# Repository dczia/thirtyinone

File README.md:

# thirtyinone
defcon 30 30-in-One badge

For those who don't like videos, here is a reasonable ordering of adding components:
* Pins (broken out all at once or a few at a time
* OLED Screen - top left, for pins
* Switches (next to battery, under keycaps hope)
* RGB LED - to the left of the other LEDS
* Speaker bottom right, on top of the spot of tape.  Polarity does not matter
* Battery case (big blank spot, bottom left)
* Key base (top right-should be obvious)
* Transformer (note THIS one is directional-the P side should line up with the P on the board)
* Potentiometer (next to the key base)
* Key Cap

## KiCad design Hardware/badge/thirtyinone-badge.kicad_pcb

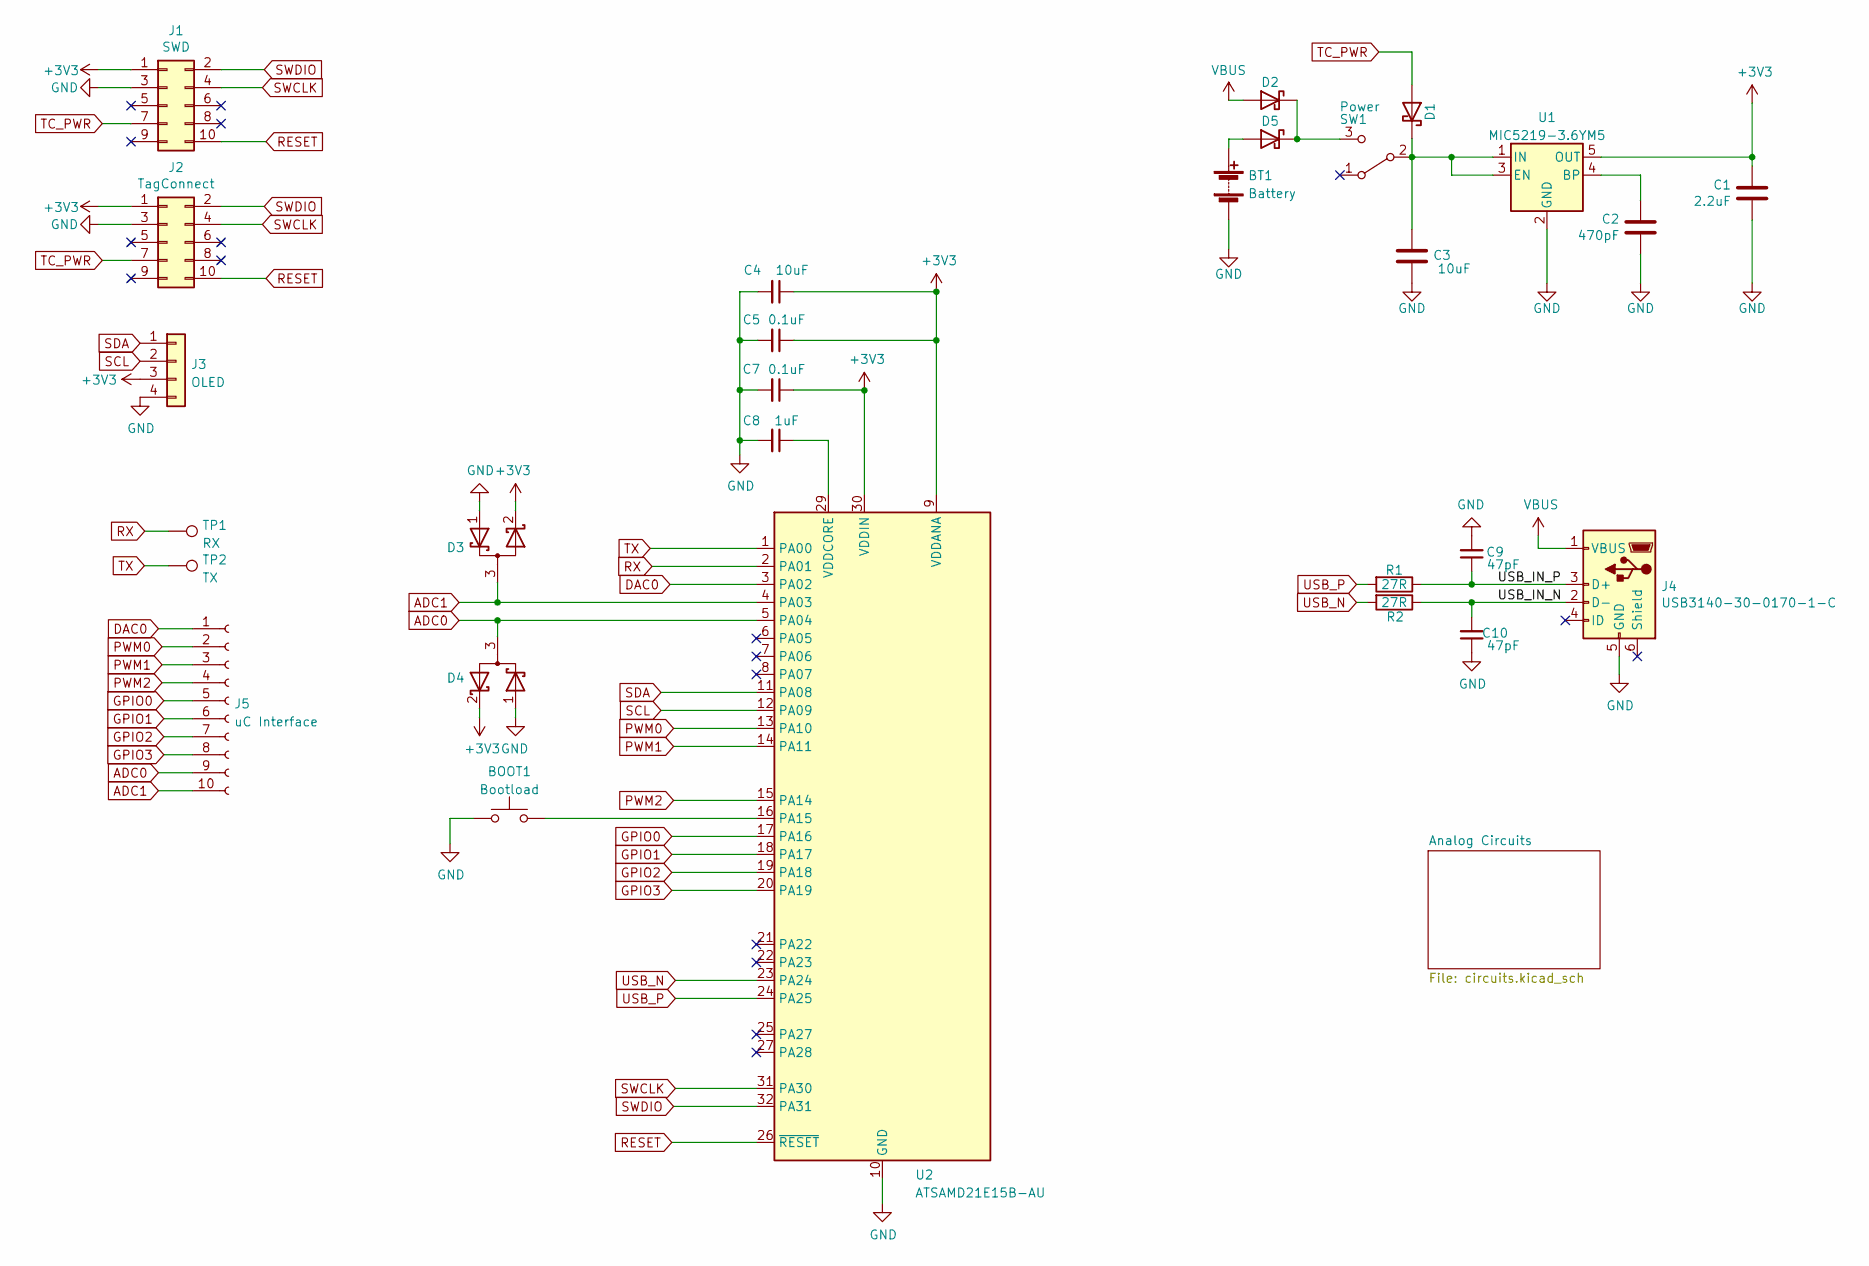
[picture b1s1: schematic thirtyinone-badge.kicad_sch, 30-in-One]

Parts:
BOOT1: Bootload; SW_Push_1P1T_NO_CK_PTS526
BT1: Battery; BatteryHolder_Keystone_2479_3xAAA
C1: 2.2uF; C_0805_2012Metric
C2: 470pF; C_0805_2012Metric
C3, C4: 10uF; C_0603_1608Metric
C5, C7: 0.1uF; C_0603_1608Metric
C8: 1uF; C_0603_1608Metric
C9, C10: 47pF; C_0603_1608Metric
D1, D2, D5: D_Schottky; D_SMA
D3, D4: D_Schottky_Dual_Series_ACK_Parallel; SOT-23
J1: SWD; PinHeader_2x05_P1.27mm_Vertical_Sneaky
J2: TagConnect; TC2050-NL_SMALL
J3: OLED; PinHeader_1x04_P2.54mm_Vertical
J4: USB3140-30-0170-1-C; USB31403001701C
J5: uC Interface; PinSocket_1x10_P2.54mm_Vertical
R1, R2: 27R; R_0603_1608Metric
SW1: Power; SW_E-Switch_EG1271_DPDT
TP1: RX; TestPoint_Pad_1.5x1.5mm
TP2: TX; TestPoint_Pad_1.5x1.5mm
U1: MIC5219-3.6YM5; SOT-23-5
U2: ATSAMD21E15B-AU; TQFP-32_7x7mm_P0.8mm

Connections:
+3V3: C1.1, C4.1, C5.1, C7.1, D3.2 (K), D4.2 (K), J1.1, J2.1, J3.3, U1.5 (OUT), U2.9 (VDDANA), U2.30 (VDDIN); also elsewhere on the board
/USB_IN_N: C10.2, J4.2 (D-), R2.1
/USB_IN_P: C9.1, J4.3 (D+), R1.1
ADC0: D4.3 (A), J5.9, U2.5 (PA04)
ADC1: D3.3 (A), J5.10, U2.4 (PA03)
DAC0: J5.1, U2.3 (PA02)
GND: BOOT1.1, BT1.2 (-), C1.2, C2.2, C3.2, C4.2, C5.2, C7.2, C8.2, C9.2, C10.1, D3.1 (K), D4.1 (K), J1.3, J2.3, J3.4, J4.5 (GND), U1.2 (GND), U2.10 (GND), U2.28 (GND); also elsewhere on the board
GPIO0: J5.5, U2.17 (PA16)
GPIO1: J5.6, U2.18 (PA17)
GPIO2: J5.7, U2.19 (PA18)
GPIO3: J5.8, U2.20 (PA19)
unnamed: BOOT1.2, U2.16 (PA15)
unnamed: BT1.1 (+), D5.2 (A)
unnamed: C2.1, U1.4 (BP)
unnamed: C3.1, D1.1 (K), SW1.2 (B), U1.1 (IN), U1.3 (EN)
unnamed: C8.1, U2.29 (VDDCORE)
unnamed: D2.1 (K), D5.1 (K), SW1.3 (C)
PWM0: J5.2, U2.13 (PA10)
PWM1: J5.3, U2.14 (PA11)
PWM2: J5.4, U2.15 (PA14)
RESET: J1.10, J2.10, U2.26 (~RESET)
RX: TP1.1, U2.2 (PA01)
SCL: J3.2, U2.12 (PA09)
SDA: J3.1, U2.11 (PA08)
SWCLK: J1.4, J2.4, U2.31 (PA30)
SWDIO: J1.2, J2.2, U2.32 (PA31)
TC_PWR: D1.2 (A), J1.7, J2.7
TX: TP2.1, U2.1 (PA00)
USB_N: R2.2, U2.23 (PA24)
USB_P: R1.2, U2.24 (PA25)
VBUS: D2.2 (A), J4.1 (VBUS)

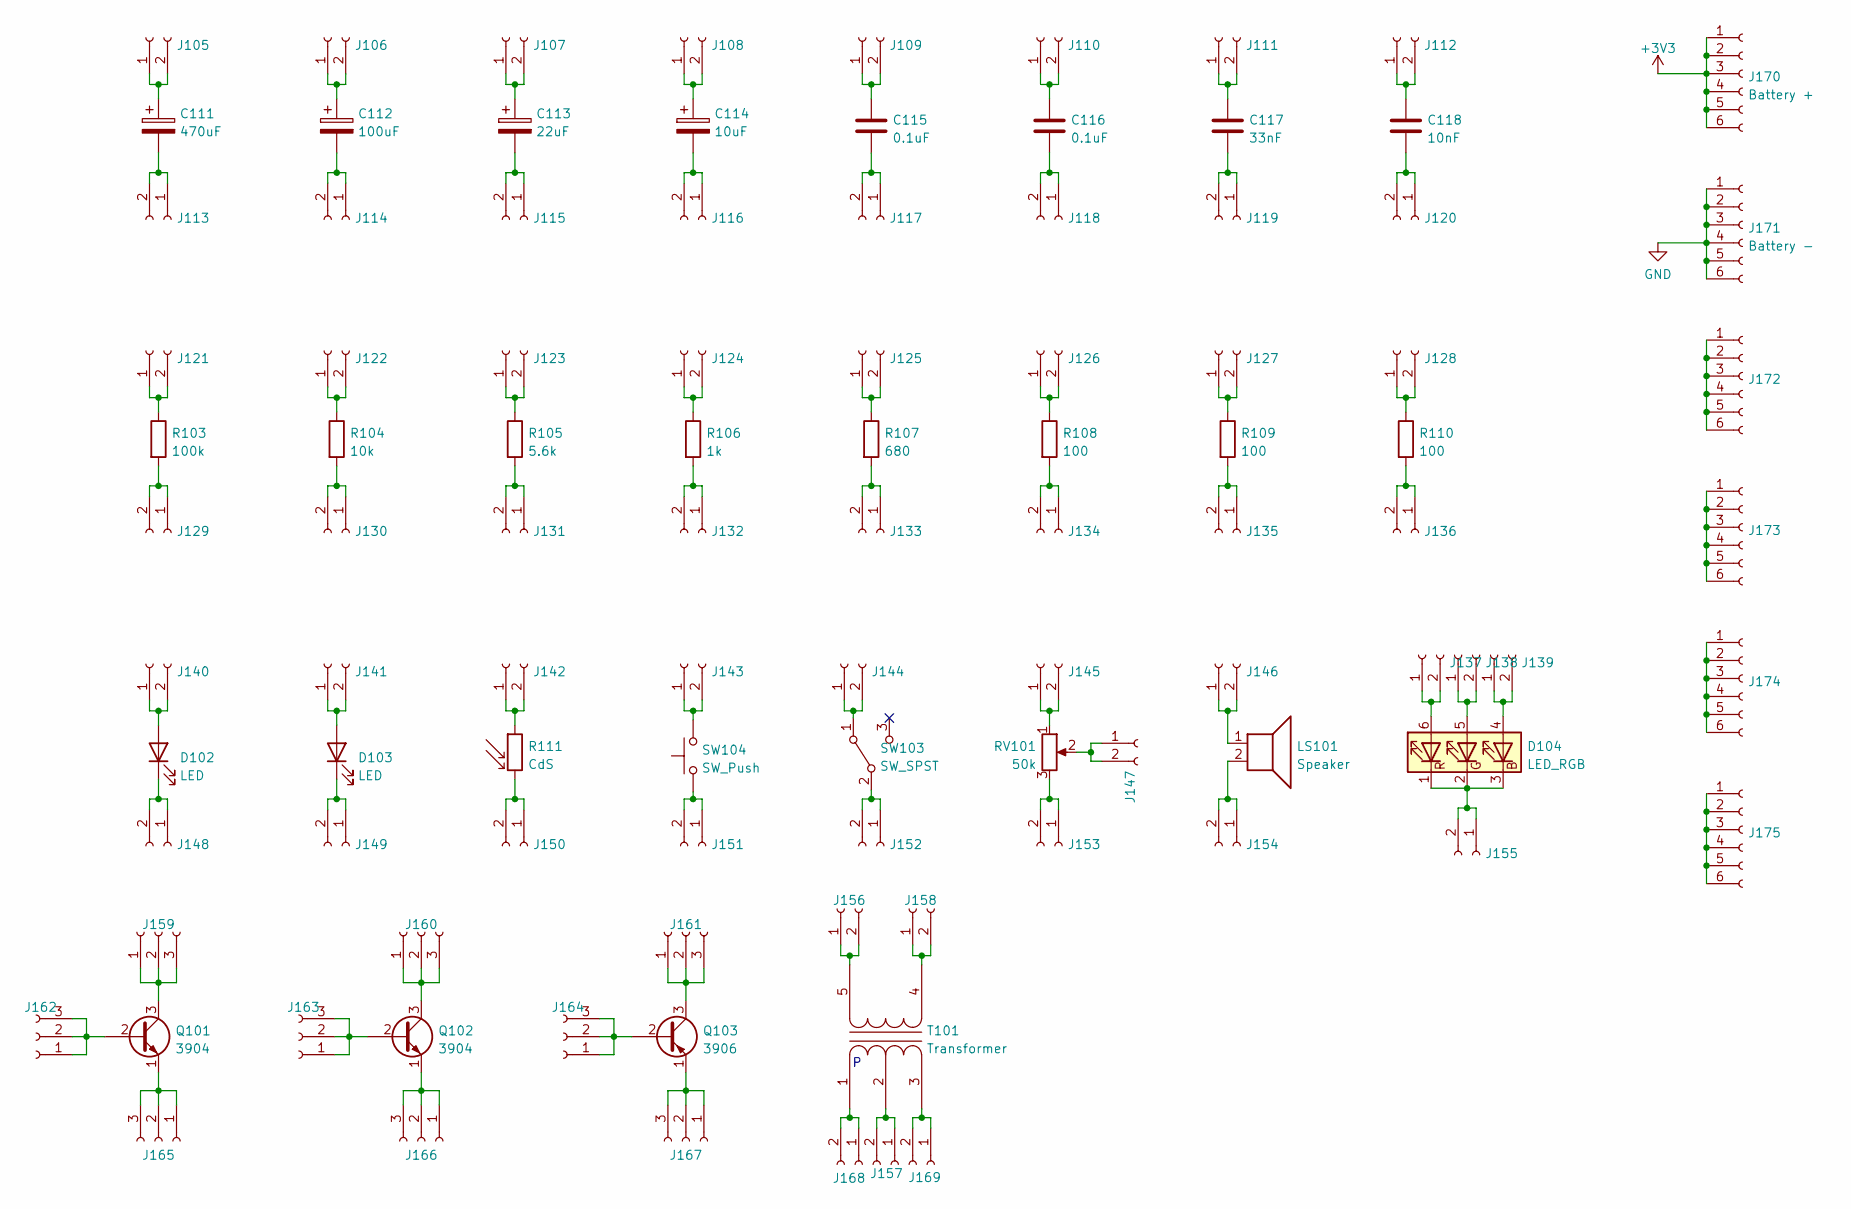
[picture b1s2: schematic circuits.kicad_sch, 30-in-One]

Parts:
C111: 470uF; CP_Elec_8x10.5
C112: 100uF; CP_Elec_5x5.4
C113: 22uF; C_0805_2012Metric
C114: 10uF; C_0603_1608Metric
C115, C116: 0.1uF; C_0603_1608Metric
C117: 33nF; C_0603_1608Metric
C118: 10nF; C_0603_1608Metric
D102, D103: LED; LED_0805_2012Metric
D104: LED_RGB; LED_RGB_PLCC-6
J105, J106, J107, J108, J109, J110, J111, J112, J113, J114, J115, J116, J117, J118, J119, J120, J121, J122, J123, J124, J125, J126, J127, J128, J129, J130, J131, J132, J133, J134, J135, J136, J137, J138, J139, J140, J141, J142, J143, J144, J145, J146, J147, J148, J149, J150, J151, J152, J153, J154, J155, J156, J157, J158, J168, J169: Conn_01x02_Female; PinSocket_1x02_P2.54mm_Vertical
J159, J160, J161, J162, J163, J164, J165, J166, J167: Conn_01x03_Female; PinSocket_1x03_P2.54mm_Vertical
J170: Battery +; PinSocket_1x06_P2.54mm_Vertical
J171: Battery -; PinSocket_1x06_P2.54mm_Vertical
J172, J173, J174, J175: Spare; PinSocket_1x06_P2.54mm_Vertical
LS101: Speaker
Q101, Q102: 3904; SOT-23
Q103: 3906; SOT-23
R103: 100k; R_0603_1608Metric
R104: 10k; R_0603_1608Metric
R105: 5.6k; R_0603_1608Metric
R106: 1k; R_0603_1608Metric
R107: 680; R_0603_1608Metric
R108, R109, R110: 100; R_0603_1608Metric
R111: CdS; CdS Cell
RV101: 50k; Potentiometer_Alps_RK09K_Single_Vertical
SW103: SW_SPST; SW_E-Switch_EG1271_DPDT
SW104: SW_Push; CHERRY_SMDLED_100H
T101: Transformer; 42TL Transformer

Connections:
+3V3: J170.1, J170.2, J170.3, J170.4, J170.5, J170.6; also elsewhere on the board
GND: J171.1, J171.2, J171.3, J171.4, J171.5, J171.6; also elsewhere on the board
unnamed: C111.1, J105.1, J105.2
unnamed: C111.2, J113.1, J113.2
unnamed: C112.1, J106.1, J106.2
unnamed: C112.2, J114.1, J114.2
unnamed: C113.1, J107.1, J107.2
unnamed: C113.2, J115.1, J115.2
unnamed: C114.1, J108.1, J108.2
unnamed: C114.2, J116.1, J116.2
unnamed: C115.1, J109.1, J109.2
unnamed: C115.2, J117.1, J117.2
unnamed: C116.1, J110.1, J110.2
unnamed: C116.2, J118.1, J118.2
unnamed: C117.1, J111.1, J111.2
unnamed: C117.2, J119.1, J119.2
unnamed: C118.1, J112.1, J112.2
unnamed: C118.2, J120.1, J120.2
unnamed: D102.1 (K), J148.1, J148.2
unnamed: D102.2 (A), J140.1, J140.2
unnamed: D103.1 (K), J149.1, J149.2
unnamed: D103.2 (A), J141.1, J141.2
unnamed: D104.1 (RK), D104.2 (GK), D104.3 (BK), J155.1, J155.2
unnamed: D104.4 (BA), J139.1, J139.2
unnamed: D104.5 (GA), J138.1, J138.2
unnamed: D104.6 (RA), J137.1, J137.2
unnamed: J121.1, J121.2, R103.1
unnamed: J122.1, J122.2, R104.1
unnamed: J123.1, J123.2, R105.1
unnamed: J124.1, J124.2, R106.1
unnamed: J125.1, J125.2, R107.1
unnamed: J126.1, J126.2, R108.1
unnamed: J127.1, J127.2, R109.1
unnamed: J128.1, J128.2, R110.1
unnamed: J129.1, J129.2, R103.2
unnamed: J130.1, J130.2, R104.2
unnamed: J131.1, J131.2, R105.2
unnamed: J132.1, J132.2, R106.2
unnamed: J133.1, J133.2, R107.2
unnamed: J134.1, J134.2, R108.2
unnamed: J135.1, J135.2, R109.2
unnamed: J136.1, J136.2, R110.2
unnamed: J142.1, J142.2, R111.1
unnamed: J143.1, J143.2, SW104.2
unnamed: J144.1, J144.2, SW103.1 (A)
unnamed: J145.1, J145.2, RV101.1
unnamed: J146.1, J146.2, LS101.1
unnamed: J147.1, J147.2, RV101.2
unnamed: J150.1, J150.2, R111.2
unnamed: J151.1, J151.2, SW104.1
unnamed: J152.1, J152.2, SW103.2 (B)
unnamed: J153.1, J153.2, RV101.3
unnamed: J154.1, J154.2, LS101.2
unnamed: J156.1, J156.2, T101.5 (S2)
unnamed: J157.1, J157.2, T101.2 (PM)
unnamed: J158.1, J158.2, T101.4 (S1)
unnamed: J159.1, J159.2, J159.3, Q101.3 (C)
unnamed: J160.1, J160.2, J160.3, Q102.3 (C)
unnamed: J161.1, J161.2, J161.3, Q103.3 (C)
unnamed: J162.1, J162.2, J162.3, Q101.2 (B)
unnamed: J163.1, J163.2, J163.3, Q102.2 (B)
unnamed: J164.1, J164.2, J164.3, Q103.2 (B)
unnamed: J165.1, J165.2, J165.3, Q101.1 (E)
unnamed: J166.1, J166.2, J166.3, Q102.1 (E)
unnamed: J167.1, J167.2, J167.3, Q103.1 (E)
unnamed: J168.1, J168.2, T101.1 (PR1)
unnamed: J169.1, J169.2, T101.3 (PR2)
unnamed: J172.1, J172.2, J172.3, J172.4, J172.5, J172.6
unnamed: J173.1, J173.2, J173.3, J173.4, J173.5, J173.6
unnamed: J174.1, J174.2, J174.3, J174.4, J174.5, J174.6
unnamed: J175.1, J175.2, J175.3, J175.4, J175.5, J175.6

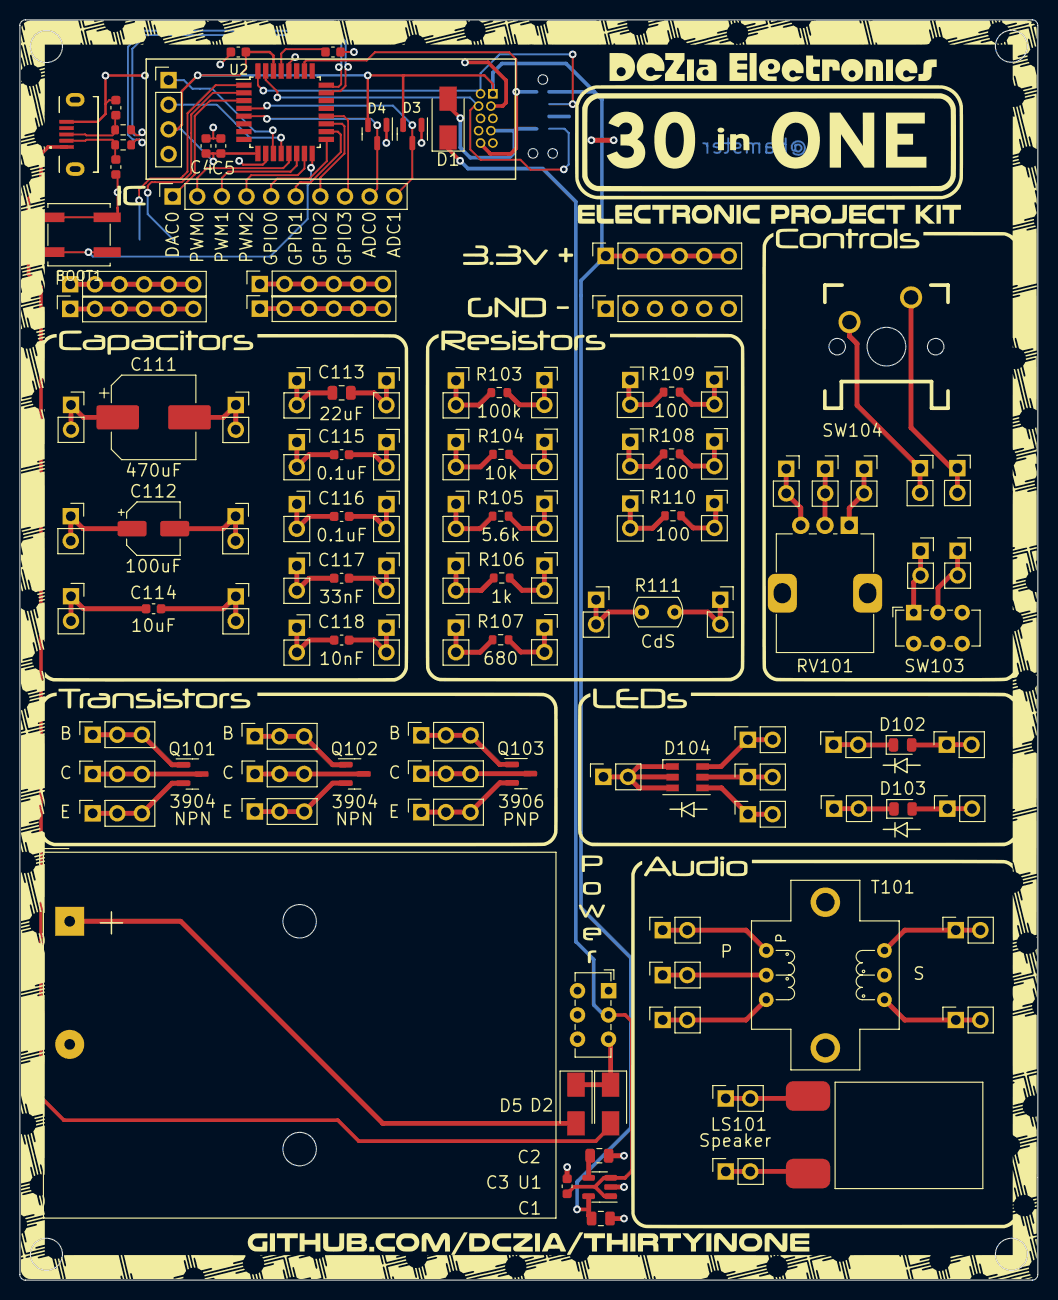
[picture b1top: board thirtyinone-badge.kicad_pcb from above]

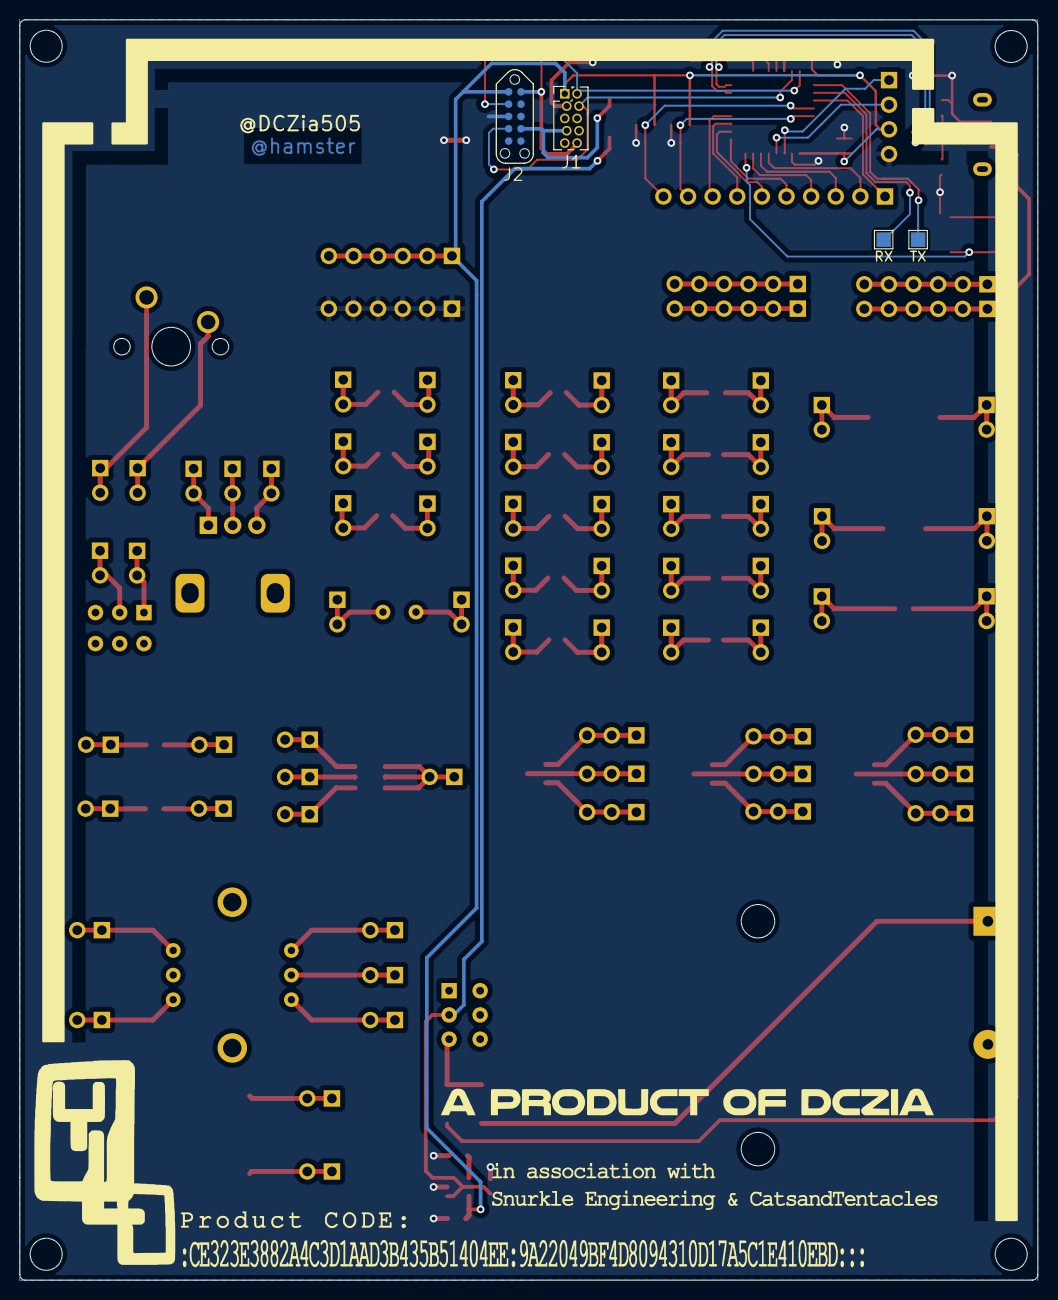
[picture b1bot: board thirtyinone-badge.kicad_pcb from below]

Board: 2 copper layers, 105.0 x 130.0 mm, 127 parts (4 on the bottom side), 100 nets.

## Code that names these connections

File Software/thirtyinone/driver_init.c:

/*
 * Code generated from Atmel Start.
 *
 * This file will be overwritten when reconfiguring your Atmel Start project.
 * Please copy examples or other code you want to keep to a separate file
 * to avoid losing it when reconfiguring.
 */

#include "driver_init.h"
#include <peripheral_clk_config.h>
#include <utils.h>
#include <hal_init.h>
#include <hpl_gclk_base.h>
#include <hpl_pm_base.h>

#include <hpl_adc_base.h>
#include <hpl_rtc_base.h>

struct timer_descriptor TIMER_0;

struct adc_sync_descriptor ADC_0;

struct i2c_m_sync_desc I2C_0;

struct usart_sync_descriptor USART_0;

struct dac_sync_descriptor DAC_0;

void ADC_0_PORT_init(void)
{

	// Disable digital pin circuitry
	gpio_set_pin_direction(PB08, GPIO_DIRECTION_IN);
	gpio_set_pin_level(PB08, false);
	gpio_set_pin_pull_mode(PB08, GPIO_PULL_DOWN);

	//gpio_set_pin_function(PB08, PINMUX_PB08B_ADC_AIN2);
	
	
	// Disable digital pin circuitry
	gpio_set_pin_direction(PB09, GPIO_DIRECTION_IN);
	gpio_set_pin_level(PB09, false);
	gpio_set_pin_pull_mode(PB09, GPIO_PULL_DOWN);

	//gpio_set_pin_function(PB09, PINMUX_PB09B_ADC_AIN3);
}

void ADC_0_CLOCK_init(void)
{
	_pm_enable_bus_clock(PM_BUS_APBC, ADC);
	_gclk_enable_channel(ADC_GCLK_ID, CONF_GCLK_ADC_SRC);
}

void ADC_0_init(void)
{
	ADC_0_CLOCK_init();
	ADC_0_PORT_init();
	adc_sync_init(&ADC_0, ADC, (void *)NULL);
}

void I2C_0_PORT_init(void)
{

	gpio_set_pin_pull_mode(PA08,
	                       // <y> Pull configuration
	                       // <id> pad_pull_config
	                       // <GPIO_PULL_OFF"> Off
	                       // <GPIO_PULL_UP"> Pull-up
	                       // <GPIO_PULL_DOWN"> Pull-down
	                       GPIO_PULL_OFF);

	gpio_set_pin_function(PA08, PINMUX_PA08C_SERCOM0_PAD0);

	gpio_set_pin_pull_mode(PA09,
	                       // <y> Pull configuration
	                       // <id> pad_pull_config
	                       // <GPIO_PULL_OFF"> Off
	                       // <GPIO_PULL_UP"> Pull-up
	                       // <GPIO_PULL_DOWN"> Pull-down
	                       GPIO_PULL_OFF);

	gpio_set_pin_function(PA09, PINMUX_PA09C_SERCOM0_PAD1);
}

void I2C_0_CLOCK_init(void)
{
	_pm_enable_bus_clock(PM_BUS_APBC, SERCOM0);
	_gclk_enable_channel(SERCOM0_GCLK_ID_CORE, CONF_GCLK_SERCOM0_CORE_SRC);
	_gclk_enable_channel(SERCOM0_GCLK_ID_SLOW, CONF_GCLK_SERCOM0_SLOW_SRC);
}

void I2C_0_init(void)
{
	I2C_0_CLOCK_init();
	i2c_m_sync_init(&I2C_0, SERCOM0);
	I2C_0_PORT_init();
}

void USART_0_PORT_init(void)
{

	gpio_set_pin_function(PA00, PINMUX_PA00D_SERCOM1_PAD0);

	gpio_set_pin_function(PA01, PINMUX_PA01D_SERCOM1_PAD1);
}

void USART_0_CLOCK_init(void)
{
	_pm_enable_bus_clock(PM_BUS_APBC, SERCOM1);
	_gclk_enable_channel(SERCOM1_GCLK_ID_CORE, CONF_GCLK_SERCOM1_CORE_SRC);
}

void USART_0_init(void)
{
	USART_0_CLOCK_init();
	usart_sync_init(&USART_0, SERCOM1, (void *)NULL);
	USART_0_PORT_init();
}

/**
 * \brief Timer initialization function
 *
 * Enables Timer peripheral, clocks and initializes Timer driver
 */
static void TIMER_0_init(void)
{
	_pm_enable_bus_clock(PM_BUS_APBA, RTC);
	_gclk_enable_channel(RTC_GCLK_ID, CONF_GCLK_RTC_SRC);
	timer_init(&TIMER_0, RTC, _rtc_get_timer());
}

void DAC_0_PORT_init(void)
{

	// Disable digital pin circuitry
	gpio_set_pin_direction(PA02, GPIO_DIRECTION_OFF);

	gpio_set_pin_function(PA02, PINMUX_PA02B_DAC_VOUT);
}

void DAC_0_CLOCK_init(void)
{

	_pm_enable_bus_clock(PM_BUS_APBC, DAC);
	_gclk_enable_channel(DAC_GCLK_ID, CONF_GCLK_DAC_SRC);
}

void DAC_0_init(void)
{
	DAC_0_CLOCK_init();
	dac_sync_init(&DAC_0, DAC);
	DAC_0_PORT_init();
}

void system_init(void)
{
	init_mcu();

	// GPIO on PA04

	gpio_set_pin_level(PWM0,
	                   // <y> Initial level
	                   // <id> pad_initial_level
	                   // <false"> Low
	                   // <true"> High
	                   false);

	// Set pin direction to output
	gpio_set_pin_direction(PWM0, GPIO_DIRECTION_OUT);

	gpio_set_pin_function(PWM0, GPIO_PIN_FUNCTION_OFF);

	// GPIO on PA05

	gpio_set_pin_level(PWM1,
	                   // <y> Initial level
	                   // <id> pad_initial_level
	                   // <false"> Low
	                   // <true"> High
	                   false);

	// Set pin direction to output
	gpio_set_pin_direction(PWM1, GPIO_DIRECTION_OUT);

	gpio_set_pin_function(PWM1, GPIO_PIN_FUNCTION_OFF);

	// GPIO on PA10

	gpio_set_pin_level(PWM2,
	                   // <y> Initial level
	                   // <id> pad_initial_level
	                   // <false"> Low
	                   // <true"> High
	                   false);

	// Set pin direction to output
	gpio_set_pin_direction(PWM2, GPIO_DIRECTION_OUT);

	gpio_set_pin_function(PWM2, GPIO_PIN_FUNCTION_OFF);

	// GPIO on PA15

	// Set pin direction to input
	gpio_set_pin_direction(BOOTLOAD, GPIO_DIRECTION_IN);

	gpio_set_pin_pull_mode(BOOTLOAD,
	                       // <y> Pull configuration
	                       // <id> pad_pull_config
	                       // <GPIO_PULL_OFF"> Off
	                       // <GPIO_PULL_UP"> Pull-up
	                       // <GPIO_PULL_DOWN"> Pull-down
	                       GPIO_PULL_UP);

	gpio_set_pin_function(BOOTLOAD, GPIO_PIN_FUNCTION_OFF);

	// GPIO on PA18

	// Set pin direction to input
	gpio_set_pin_direction(GPIO0, GPIO_DIRECTION_IN);

	gpio_set_pin_pull_mode(GPIO0,
	                       // <y> Pull configuration
	                       // <id> pad_pull_config
	                       // <GPIO_PULL_OFF"> Off
	                       // <GPIO_PULL_UP"> Pull-up
	                       // <GPIO_PULL_DOWN"> Pull-down
	                       GPIO_PULL_DOWN);

	gpio_set_pin_function(GPIO0, GPIO_PIN_FUNCTION_OFF);

	// GPIO on PA19

	gpio_set_pin_level(GPIO1,
	                   // <y> Initial level
	                   // <id> pad_initial_level
	                   // <false"> Low
	                   // <true"> High
	                   false);

	// Set pin direction to output
	gpio_set_pin_direction(GPIO1, GPIO_DIRECTION_OUT);

	gpio_set_pin_function(GPIO1, GPIO_PIN_FUNCTION_OFF);

	// GPIO on PA20

	gpio_set_pin_level(GPIO2,
	                   // <y> Initial level
	                   // <id> pad_initial_level
	                   // <false"> Low
	                   // <true"> High
	                   false);

	// Set pin direction to output
	gpio_set_pin_direction(GPIO2, GPIO_DIRECTION_OUT);

	gpio_set_pin_function(GPIO2, GPIO_PIN_FUNCTION_OFF);

	// GPIO on PA21

	gpio_set_pin_level(GPIO3,
	                   // <y> Initial level
	                   // <id> pad_initial_level
	                   // <false"> Low
	                   // <true"> High
	                   false);

	// Set pin direction to output
	gpio_set_pin_direction(GPIO3, GPIO_DIRECTION_OUT);

	gpio_set_pin_function(GPIO3, GPIO_PIN_FUNCTION_OFF);

	ADC_0_init();

	I2C_0_init();

	USART_0_init();

	TIMER_0_init();

	DAC_0_init();
}

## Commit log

2022-07-24 Booklet source and PDF
    Source (.pages) file for team use only -- should not be made publicly accessible.
    PDF has corrected wiring diagrams for projects 25 and 26.
2022-08-02 Initial commit of the 1.0 as-built, missing a few items to prevent puzzle spoilage
2022-08-10 Adding software for the badge Adding corrections page and build instructions card
2022-09-11 Updated to hardware version 1.1 to reflect some footprint fixes, and swap to an alternate microcontroller due to parts availability
